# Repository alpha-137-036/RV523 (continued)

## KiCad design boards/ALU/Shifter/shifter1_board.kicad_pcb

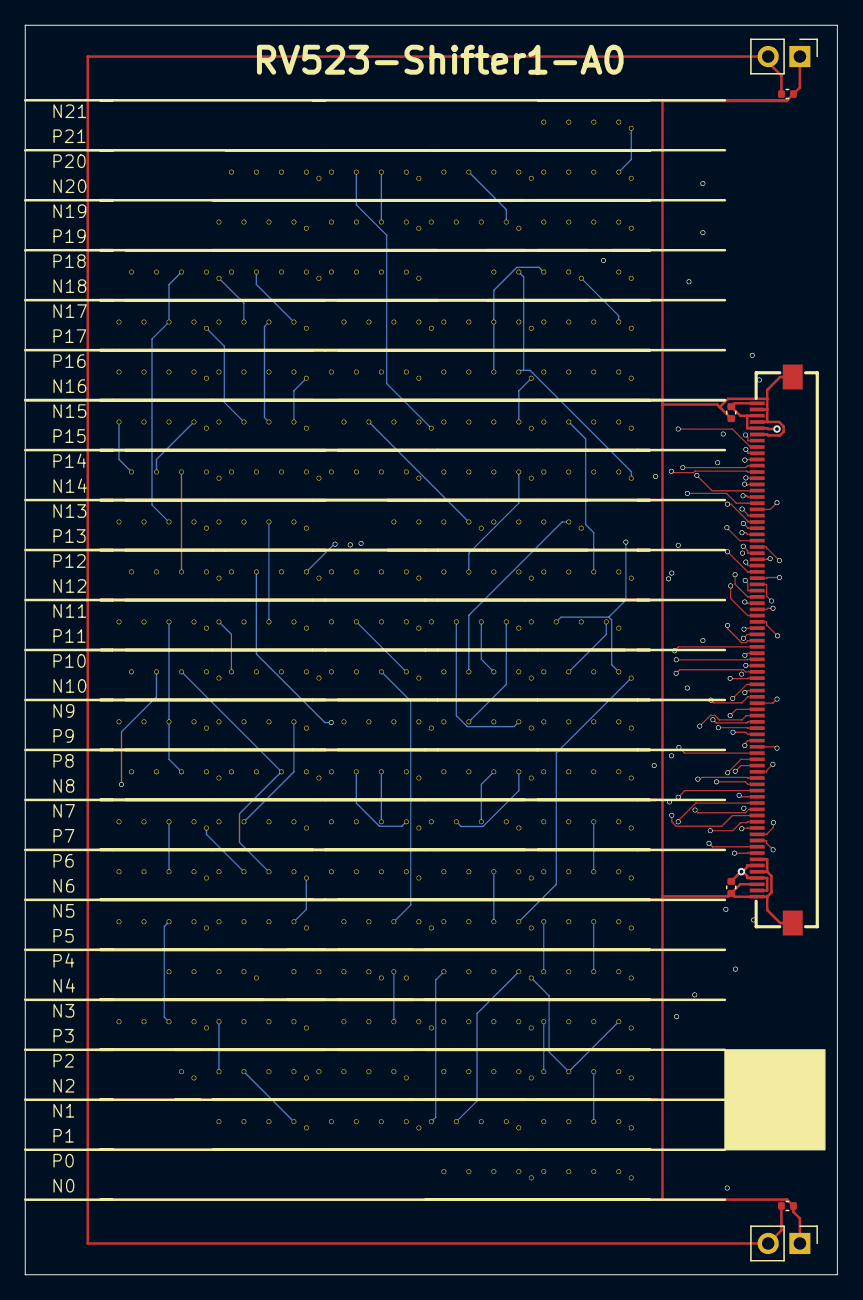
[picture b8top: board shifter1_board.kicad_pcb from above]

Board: 4 copper layers, 65.0 x 100.0 mm, 172 parts (0 on the bottom side), 138 nets.

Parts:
C1, C2, C3, C4: C_0402_1005Metric
j1: FPC-SMD_THD0518-80CL-GF
j2, j3: PinHeader_1x02_P2.54mm_Vertical
sh1._185_, sh1._186_, sh1._187_, sh1._188_, sh1._189_, sh1._190_, sh1._191_, sh1._192_, sh1._193_, sh1._194_, sh1._195_, sh1._196_, sh1._197_, sh1._198_, sh1._199_, sh1._200_, sh1._201_, sh1._202_, sh1._203_, sh1._204_, sh1._205_, sh1._206_, sh1._207_, sh1._208_, sh1._209_, sh1._210_, sh1._211_, sh1._212_, sh1._213_, sh1._214_, sh1._215_, sh1._216_, sh1._220_, sh1._221_, sh1._222_, sh1._223_, sh1._224_, sh1._225_, sh1._226_, sh1._227_, sh1._228_, sh1._229_, sh1._230_, sh1._231_, sh1._232_, sh1._233_, sh1._234_, sh1._235_, sh1._236_, sh1._237_, sh1._238_, sh1._239_, sh1._240_, sh1._241_, sh1._242_, sh1._243_, sh1._244_, sh1._245_, sh1._246_, sh1._247_, sh1._248_, sh1._249_, sh1._250_, sh1._251_, sh1._252_, sh1._253_, sh1._254_, sh1._255_, sh1._256_, sh1._257_, sh1._258_, sh1._259_, sh1._260_, sh1._261_, sh1._262_, sh1._263_, sh1._264_, sh1._265_, sh1._266_, sh1._267_, sh1._268_, sh1._269_, sh1._270_, sh1._271_, sh1._272_, sh1._273_, sh1._274_, sh1._275_, sh1._276_, sh1._277_, sh1._278_, sh1._279_, sh1._280_, sh1._281_, sh1._282_, sh1._283_: AOI22
sh1._217_, sh1._218_, sh1._219_: NOT
sh1.decap0_L, sh1.decap0_M, sh1.decap0_R, sh1.decap1_L, sh1.decap1_M, sh1.decap1_R, sh1.decap2_L, sh1.decap2_M, sh1.decap2_R, sh1.decap3_L, sh1.decap3_M, sh1.decap3_R, sh1.decap4_L, sh1.decap4_M, sh1.decap4_R, sh1.decap5_L, sh1.decap5_M, sh1.decap5_R, sh1.decap6_L, sh1.decap6_M, sh1.decap6_R, sh1.decap7_L, sh1.decap7_M, sh1.decap7_R, sh1.decap8_L, sh1.decap8_M, sh1.decap8_R, sh1.decap9_L, sh1.decap9_M, sh1.decap9_R, sh1.decap10_L, sh1.decap10_M, sh1.decap10_R, sh1.decap11_L, sh1.decap11_M, sh1.decap11_R, sh1.decap12_L, sh1.decap12_M, sh1.decap12_R, sh1.decap13_L, sh1.decap13_M, sh1.decap13_R, sh1.decap14_L, sh1.decap14_M, sh1.decap14_R, sh1.decap15_L, sh1.decap15_M, sh1.decap15_R, sh1.decap16_L, sh1.decap16_M, sh1.decap16_R, sh1.decap17_L, sh1.decap17_M, sh1.decap17_R, sh1.decap18_L, sh1.decap18_M, sh1.decap18_R, sh1.decap19_L, sh1.decap19_M, sh1.decap19_R, sh1.decap20_L, sh1.decap20_M, sh1.decap20_R, sh1.decap21_L, sh1.decap21_M, sh1.decap21_R: DECAP

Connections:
A0: j1.74 (pins.74), sh1._219_.A, sh1._252_.B2, sh1._263_.B2
A.0: j1.71 (pins.71), sh1._193_.B1, sh1._200_.A2
A.1: j1.69 (pins.69), sh1._192_.B2, sh1._211_.A2
A.2: j1.67 (pins.67), sh1._190_.A2, sh1._191_.B2
A.3: j1.65 (pins.65), sh1._189_.B2, sh1._194_.A2
A.4: j1.63 (pins.63), sh1._188_.B2, sh1._195_.A2
A.5: j1.61 (pins.61), sh1._187_.B2, sh1._196_.A2
A.6: j1.59 (pins.59), sh1._186_.B2, sh1._197_.A2
A.7: j1.57 (pins.57), sh1._185_.B2, sh1._198_.A2
A.8: j1.55 (pins.55), sh1._199_.A2, sh1._216_.B2
A.9: j1.53 (pins.53), sh1._201_.A2, sh1._215_.B2
A.10: j1.51 (pins.51), sh1._202_.A2, sh1._214_.B2
A.11: j1.49 (pins.49), sh1._203_.A2, sh1._213_.B2
A.12: j1.47 (pins.47), sh1._204_.A2, sh1._212_.B2
A.13: j1.45 (pins.45), sh1._205_.A2, sh1._210_.B2
A.14: j1.43 (pins.43), sh1._206_.A2, sh1._209_.B2
A.15: j1.41 (pins.41), sh1._207_.A2, sh1._208_.B2
A.16: j1.39 (pins.39), sh1._207_.B2, sh1._208_.A2
A.17: j1.37 (pins.37), sh1._206_.B2, sh1._209_.A2
A.18: j1.35 (pins.35), sh1._205_.B2, sh1._210_.A2
A.19: j1.33 (pins.33), sh1._204_.B2, sh1._212_.A2
A.20: j1.31 (pins.31), sh1._203_.B2, sh1._213_.A2
A.21: j1.29 (pins.29), sh1._202_.B2, sh1._214_.A2
A.22: j1.27 (pins.27), sh1._201_.B2, sh1._215_.A2
A.23: j1.25 (pins.25), sh1._199_.B2, sh1._216_.A2
A.24: j1.23 (pins.23), sh1._185_.A2, sh1._198_.B2
A.25: j1.21 (pins.21), sh1._186_.A2, sh1._197_.B2
A.26: j1.19 (pins.19), sh1._187_.A2, sh1._196_.B2
A.27: j1.17 (pins.17), sh1._188_.A2, sh1._195_.B2
A.28: j1.15 (pins.15), sh1._189_.A2, sh1._194_.B2
A.29: j1.13 (pins.13), sh1._190_.B2, sh1._191_.A2
A.30: j1.11 (pins.11), sh1._192_.A2, sh1._211_.B2
A.31: j1.9 (pins.9), sh1._193_.A2, sh1._200_.B2
B.0: sh1._217_.A, sh1._220_.B1, sh1._221_.B1, sh1._222_.B1, sh1._223_.B1, sh1._224_.B1, sh1._225_.B1, sh1._226_.B1, sh1._227_.B1, sh1._228_.B1, sh1._229_.B1, sh1._230_.B1, sh1._231_.B1, sh1._232_.B1, sh1._233_.B1, sh1._234_.B1, sh1._235_.B1, sh1._236_.B1, sh1._237_.B1, sh1._238_.B1, sh1._239_.B1, sh1._240_.B1, sh1._241_.B1, sh1._242_.B1, sh1._243_.B1, sh1._244_.B1, sh1._245_.B1, sh1._246_.B1, sh1._247_.B1, sh1._248_.B1, sh1._249_.B1, sh1._250_.B1, sh1._251_.B1
B.1: sh1._218_.A, sh1._252_.B1, sh1._253_.B1, sh1._254_.B1, sh1._255_.B1, sh1._256_.B1, sh1._257_.B1, sh1._258_.B1, sh1._259_.B1, sh1._260_.B1, sh1._261_.B1, sh1._262_.B1, sh1._263_.B1, sh1._264_.B1, sh1._265_.B1, sh1._266_.B1, sh1._267_.B1, sh1._268_.B1, sh1._269_.B1, sh1._270_.B1, sh1._271_.B1, sh1._272_.B1, sh1._273_.B1, sh1._274_.B1, sh1._275_.B1, sh1._276_.B1, sh1._277_.B1, sh1._278_.B1, sh1._279_.B1, sh1._280_.B1, sh1._281_.B1, sh1._282_.B1, sh1._283_.B1
F.0: j1.70 (pins.70), sh1._252_.Y
F.1: j1.68 (pins.68), sh1._263_.Y
F.2: j1.66 (pins.66), sh1._274_.Y
F.3: j1.64 (pins.64), sh1._277_.Y
F.4: j1.62 (pins.62), sh1._278_.Y
F.5: j1.60 (pins.60), sh1._279_.Y
F.6: j1.58 (pins.58), sh1._280_.Y
F.7: j1.56 (pins.56), sh1._281_.Y
F.8: j1.54 (pins.54), sh1._282_.Y
F.9: j1.52 (pins.52), sh1._283_.Y
F.10: j1.50 (pins.50), sh1._253_.Y
F.11: j1.48 (pins.48), sh1._254_.Y
F.12: j1.46 (pins.46), sh1._255_.Y
F.13: j1.44 (pins.44), sh1._256_.Y
F.14: j1.42 (pins.42), sh1._257_.Y
F.15: j1.40 (pins.40), sh1._258_.Y
F.16: j1.38 (pins.38), sh1._259_.Y
F.17: j1.36 (pins.36), sh1._260_.Y
F.18: j1.34 (pins.34), sh1._261_.Y
F.19: j1.32 (pins.32), sh1._262_.Y
F.20: j1.30 (pins.30), sh1._264_.Y
F.21: j1.28 (pins.28), sh1._265_.Y
F.22: j1.26 (pins.26), sh1._266_.Y
F.23: j1.24 (pins.24), sh1._267_.Y
F.24: j1.22 (pins.22), sh1._268_.Y
F.25: j1.20 (pins.20), sh1._269_.Y
F.26: j1.18 (pins.18), sh1._270_.Y
F.27: j1.16 (pins.16), sh1._271_.Y
F.28: j1.14 (pins.14), sh1._272_.Y
F.29: j1.12 (pins.12), sh1._273_.Y
F.30: j1.10 (pins.10), sh1._275_.Y
F.31: j1.8 (pins.8), sh1._276_.Y
GND: C1.1, C2.1, C3.1, C4.1, j1.1 (pins.1), j1.3 (pins.3), j1.5 (pins.5), j1.7 (pins.7), j1.75 (pins.75), j1.77 (pins.77), j1.79 (pins.79), j1.81 (pins.81), j1.82 (pins.82), j2.1 (pins.1), j3.1 (pins.1)
VDD: C1.2, C2.2, C3.2, C4.2, j1.2 (pins.2), j1.4 (pins.4), j1.6 (pins.6), j1.76 (pins.76), j1.78 (pins.78), j1.80 (pins.80), j2.2 (pins.2), j3.2 (pins.2)
pins.71: j1.72 (pins.72), sh1._185_.A1, sh1._186_.A1, sh1._187_.A1, sh1._188_.A1, sh1._189_.A1, sh1._190_.A1, sh1._191_.A1, sh1._192_.A1, sh1._193_.A1, sh1._194_.A1, sh1._195_.A1, sh1._196_.A1, sh1._197_.A1, sh1._198_.A1, sh1._199_.A1, sh1._200_.A1, sh1._201_.A1, sh1._202_.A1, sh1._203_.A1, sh1._204_.A1, sh1._205_.A1, sh1._206_.A1, sh1._207_.A1, sh1._208_.A1, sh1._209_.A1, sh1._210_.A1, sh1._211_.A1, sh1._212_.A1, sh1._213_.A1, sh1._214_.A1, sh1._215_.A1, sh1._216_.A1
pins.72: j1.73 (pins.73), sh1._185_.B1, sh1._186_.B1, sh1._187_.B1, sh1._188_.B1, sh1._189_.B1, sh1._190_.B1, sh1._191_.B1, sh1._192_.B1, sh1._193_.B2, sh1._194_.B1, sh1._195_.B1, sh1._196_.B1, sh1._197_.B1, sh1._198_.B1, sh1._199_.B1, sh1._200_.B1, sh1._201_.B1, sh1._202_.B1, sh1._203_.B1, sh1._204_.B1, sh1._205_.B1, sh1._206_.B1, sh1._207_.B1, sh1._208_.B1, sh1._209_.B1, sh1._210_.B1, sh1._211_.B1, sh1._212_.B1, sh1._213_.B1, sh1._214_.B1, sh1._215_.B1, sh1._216_.B1
sh1._035_: sh1._200_.Y, sh1._220_.A2, sh1._231_.B2
sh1._036_: sh1._202_.Y, sh1._221_.A2, sh1._222_.B2
sh1._037_: sh1._203_.Y, sh1._222_.A2, sh1._223_.B2
sh1._038_: sh1._204_.Y, sh1._223_.A2, sh1._224_.B2
sh1._039_: sh1._205_.Y, sh1._224_.A2, sh1._225_.B2
sh1._040_: sh1._206_.Y, sh1._225_.A2, sh1._226_.B2
sh1._041_: sh1._207_.Y, sh1._226_.A2, sh1._227_.B2
sh1._042_: sh1._208_.Y, sh1._227_.A2, sh1._228_.B2
sh1._043_: sh1._209_.Y, sh1._228_.A2, sh1._229_.B2
sh1._044_: sh1._210_.Y, sh1._229_.A2, sh1._230_.B2
sh1._045_: sh1._212_.Y, sh1._230_.A2, sh1._232_.B2
sh1._046_: sh1._211_.Y, sh1._231_.A2, sh1._242_.B2
sh1._047_: sh1._213_.Y, sh1._232_.A2, sh1._233_.B2
sh1._048_: sh1._214_.Y, sh1._233_.A2, sh1._234_.B2
sh1._049_: sh1._215_.Y, sh1._234_.A2, sh1._235_.B2
sh1._050_: sh1._216_.Y, sh1._235_.A2, sh1._236_.B2
sh1._051_: sh1._185_.Y, sh1._236_.A2, sh1._237_.B2
sh1._052_: sh1._186_.Y, sh1._237_.A2, sh1._238_.B2
sh1._053_: sh1._187_.Y, sh1._238_.A2, sh1._239_.B2
sh1._054_: sh1._188_.Y, sh1._239_.A2, sh1._240_.B2
sh1._055_: sh1._189_.Y, sh1._240_.A2, sh1._241_.B2
sh1._056_: sh1._191_.Y, sh1._241_.A2, sh1._243_.B2
sh1._057_: sh1._190_.Y, sh1._242_.A2, sh1._245_.B2
sh1._058_: sh1._192_.Y, sh1._243_.A2, sh1._244_.B2
sh1._059_: sh1._193_.Y, sh1._244_.A2
sh1._060_: sh1._194_.Y, sh1._245_.A2, sh1._246_.B2
sh1._061_: sh1._195_.Y, sh1._246_.A2, sh1._247_.B2
sh1._062_: sh1._196_.Y, sh1._247_.A2, sh1._248_.B2
sh1._063_: sh1._197_.Y, sh1._248_.A2, sh1._249_.B2
sh1._064_: sh1._198_.Y, sh1._249_.A2, sh1._250_.B2
sh1._065_: sh1._199_.Y, sh1._250_.A2, sh1._251_.B2
sh1._066_: sh1._201_.Y, sh1._221_.B2, sh1._251_.A2
sh1._067_: sh1._219_.Y, sh1._220_.B2
sh1._068_: sh1._217_.Y, sh1._220_.A1, sh1._221_.A1, sh1._222_.A1, sh1._223_.A1, sh1._224_.A1, sh1._225_.A1, sh1._226_.A1, sh1._227_.A1, sh1._228_.A1, sh1._229_.A1, sh1._230_.A1, sh1._231_.A1, sh1._232_.A1, sh1._233_.A1, sh1._234_.A1, sh1._235_.A1, sh1._236_.A1, sh1._237_.A1, sh1._238_.A1, sh1._239_.A1, sh1._240_.A1, sh1._241_.A1, sh1._242_.A1, sh1._243_.A1, sh1._244_.A1, sh1._245_.A1, sh1._246_.A1, sh1._247_.A1, sh1._248_.A1, sh1._249_.A1, sh1._250_.A1, sh1._251_.A1
sh1._069_: sh1._218_.Y, sh1._252_.A1, sh1._253_.A1, sh1._254_.A1, sh1._255_.A1, sh1._256_.A1, sh1._257_.A1, sh1._258_.A1, sh1._259_.A1, sh1._260_.A1, sh1._261_.A1, sh1._262_.A1, sh1._263_.A1, sh1._264_.A1, sh1._265_.A1, sh1._266_.A1, sh1._267_.A1, sh1._268_.A1, sh1._269_.A1, sh1._270_.A1, sh1._271_.A1, sh1._272_.A1, sh1._273_.A1, sh1._274_.A1, sh1._275_.A1, sh1._276_.A1, sh1._277_.A1, sh1._278_.A1, sh1._279_.A1, sh1._280_.A1, sh1._281_.A1, sh1._282_.A1, sh1._283_.A1
sh1._073_.0: sh1._220_.Y, sh1._252_.A2, sh1._274_.B2
sh1._073_.1: sh1._231_.Y, sh1._263_.A2, sh1._277_.B2
sh1._073_.2: sh1._242_.Y, sh1._274_.A2, sh1._278_.B2
sh1._073_.3: sh1._245_.Y, sh1._277_.A2, sh1._279_.B2
sh1._073_.4: sh1._246_.Y, sh1._278_.A2, sh1._280_.B2
sh1._073_.5: sh1._247_.Y, sh1._279_.A2, sh1._281_.B2
sh1._073_.6: sh1._248_.Y, sh1._280_.A2, sh1._282_.B2
sh1._073_.7: sh1._249_.Y, sh1._281_.A2, sh1._283_.B2
sh1._073_.8: sh1._250_.Y, sh1._253_.B2, sh1._282_.A2
sh1._073_.9: sh1._251_.Y, sh1._254_.B2, sh1._283_.A2
sh1._073_.10: sh1._221_.Y, sh1._253_.A2, sh1._255_.B2
sh1._073_.11: sh1._222_.Y, sh1._254_.A2, sh1._256_.B2
sh1._073_.12: sh1._223_.Y, sh1._255_.A2, sh1._257_.B2
sh1._073_.13: sh1._224_.Y, sh1._256_.A2, sh1._258_.B2
sh1._073_.14: sh1._225_.Y, sh1._257_.A2, sh1._259_.B2
sh1._073_.15: sh1._226_.Y, sh1._258_.A2, sh1._260_.B2
sh1._073_.16: sh1._227_.Y, sh1._259_.A2, sh1._261_.B2
sh1._073_.17: sh1._228_.Y, sh1._260_.A2, sh1._262_.B2
sh1._073_.18: sh1._229_.Y, sh1._261_.A2, sh1._264_.B2
sh1._073_.19: sh1._230_.Y, sh1._262_.A2, sh1._265_.B2
sh1._073_.20: sh1._232_.Y, sh1._264_.A2, sh1._266_.B2
sh1._073_.21: sh1._233_.Y, sh1._265_.A2, sh1._267_.B2
sh1._073_.22: sh1._234_.Y, sh1._266_.A2, sh1._268_.B2
sh1._073_.23: sh1._235_.Y, sh1._267_.A2, sh1._269_.B2
sh1._073_.24: sh1._236_.Y, sh1._268_.A2, sh1._270_.B2
sh1._073_.25: sh1._237_.Y, sh1._269_.A2, sh1._271_.B2
sh1._073_.26: sh1._238_.Y, sh1._270_.A2, sh1._272_.B2
sh1._073_.27: sh1._239_.Y, sh1._271_.A2, sh1._273_.B2
sh1._073_.28: sh1._240_.Y, sh1._272_.A2, sh1._275_.B2
sh1._073_.29: sh1._241_.Y, sh1._273_.A2, sh1._276_.B2
sh1._073_.30: sh1._243_.Y, sh1._275_.A2
sh1._073_.31: sh1._244_.Y, sh1._276_.A2

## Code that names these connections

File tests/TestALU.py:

from ALU import ALU
from testboard import TestBoard
from time import sleep

alu = ALU()
testboard = TestBoard()

alu.connectTestBoard(testboard, 8)

alu.enableLEDs(True)


alu.A = 0xA5
alu.B = 0x5A
alu.Cin = 0

# while True:
#     alu.ADD = 0
#     sleep(0.20)
#     alu.ADD = 1
#     sleep(0.20)

doSweep = True

alu.ADD = 1
alu.XOR = 1
alu.AND = 0
alu.SUB = 0
alu.nSET0 = 0

if doSweep:
    for A in range(1 << alu.N):
        for B in range(1 << alu.N):
            alu.A = A
            alu.B = B
            print(f"A = {A}, B={B} ==> S={alu.S}")
else:
    alu.A = 0x5A
    alu.B = 0x33

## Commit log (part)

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2025-05-17 First version
2025-05-17 pin headers (2*17 and 2*8)
2025-05-18 Routing complete. Corrected some errors
2025-05-18 ^Move origin. Lines between all slices
2025-05-18 Schematic for 8-bit ALU
2025-05-18 schematic with solder jumpers for S31/C31
2025-05-18 Attempt to design the 8-bit ALU PCB
2025-05-19 Routed PCB. BUT SetBit0 is missing !
2025-05-19 Mounting holes. PCB title.
2025-06-09 Improve look of the bus pin numbers
2025-06-09 Cosmetic improvement of the silkscreen (position of annotations for the 2x1 pin headers)
2025-06-09 Re-route with wider tracks and vias, to avoid "Danger" notifications from JLCPCB.
2025-06-09 Pass-through connectors. Partial manual routing.
2025-06-09 Final version. Stopped trying to correct the thermal relief error. This is apparently not needed with solder reflow
2025-06-09 Remove some loose tracks
2025-06-09 Oups, orientation of the MCP23017 chips was somehow wrong by 180 degrees ! Thanks JLCPCB for their component viewer !!
2025-06-09 Manual routing the main bus
2025-06-09 Use larger vias. Auto-routing is still working !! That's good placement :)
2025-06-09 Yes: complete auto-routing; "stick" form factor. Silk screen complete.
2025-06-09 First version of TestBoard. Lacking the 2.54mm pin headers
2025-06-09 Production files
2025-06-09 Complete routing. BEAUTIFUL !!!
2025-06-09 Manual routing and SSOP. Only routed the signal lines. Beautiful, isn't it ?
2025-06-09 Fine tuning the PCB
2025-06-09 Attempt to resolve one more solder mask / pad violation
2025-06-09 Don't make silk screen overlap with pads. Horror: I realized the auo-router has NOT completed its job.... many connections are not done !
2025-06-09 Bus pin silkscreen labels
2025-06-14 Variant of test board with 4 20P connectors rather than 1 80P
2025-06-14 Silkscreen cleanup. Production files.
2025-06-14 Use M2 mounting holes rather than 2.5mm holes
2025-06-28 New idea: implementation using only MOSFET transistors ! Spice simulation of ALU...
2025-07-01 First steps to design a "standard cell library" of cells using only discrete transistors.
    Project trajectory is changing !
2025-07-01 Experiments with a Verilog->Kicad workshop
2025-07-02 NOT layout
2025-07-02 All gates layout on a strict 2.5mm grid. Flipped versions of all three layouts
2025-07-02 Update footprint to better match the layout. Use silkscreen to describe the power rails
2025-07-02 First prototype for the generator of the final board
2025-07-03 flip the cells to share power lines
2025-07-13 Move standard cell library to lib/ NOR Refined yosys to kicad netlist converter
2025-07-13 Analog simulation of NAND3 cell
2025-07-13 NOR3 cell with spice simulation and PCB design
2025-07-13 NOT cell: spice simulation, netlist generation
2025-07-13 Generate spice circuit using python script
2025-07-13 same for NAND3
2025-07-13 same for NAND
2025-07-13 Automate better the generation of test vectors
2025-07-13 Move pin definition to gate's physical .v
2025-07-13 OAI22 cell
2025-07-14 Update pin names in behavioral verilog
2025-07-14 OAI21 cell
2025-07-14 AOI211 cell
2025-07-14 OAI211 cell
2025-07-14 Footprints for all implemented cells
2025-07-14 Somehow NAND PCB was botched. Changed pin position of B, too
2025-07-14 The layout of the NOT gate was also botched (PMOS pinout wrong)
2025-07-14 First tries toward flip-flop and latches: SR_LATCH cell
2025-07-14 D_LATCH, with tests
2025-07-14 High-density layout with pitch of 1.1mm, which gains 23% !!
2025-07-15 Update AOI22 footprint
2025-07-15 Update OAI22 footprint
2025-07-15 Update OAI21 footprint
2025-07-15 Update NAND3 footprint
2025-07-15 Update NAND footprint
2025-07-15 Update NOR footprint
2025-07-15 Update NOT footprint
2025-07-15 Experiments on ALU
2025-07-15 DECAP pseudo-cell
2025-07-15 Continue refactoring
2025-07-15 TINV Tristate Inverter (no test yet)
2025-07-16 D_LATCH now uses TINV
2025-07-16 Rename EN/nEN into CLK/nCLK for D_LATCH
2025-07-20 Rename NAND into NAND2 and its inputs A and B into A1 and A2 (general convention when the pins can be swapped)
2025-07-20 Same for NOR->NOR2
2025-07-20 Same for NOR3
2025-07-20 Conversion tool had a bug
2025-07-20 Add thresholds to RV523.lib, this seems to be necessary for the placer
2025-07-20 Version script to autoplace using OpenROAD
2025-07-23 Y pad was misplaced
2025-07-23 NAND4 gate
2025-07-23 NAND4 and NOR4 footprints
2025-07-23 Unlock tracks in OAI211
2025-07-25 Footprint of all cells now use 1mm*4mm grid rather than 1.1mm*4.4mm
2025-07-25 New grid pitch
2025-07-25 Experiment with pads at Y=1.8/2.2 rather than 1.7/2.3 and not moving the transistors up and down, otherwise, Y-clearance of 0.4mm cannot be ensured
2025-07-25 Make the pads of my SOT523 footprint very slightly smaller, which is enough to route all the cells and leave the mosfets exactly on the grid
2025-07-26 Add the value "NMOS" and "PMOS" to the transistor modules
2025-07-26 Propagate MOSFET values to the cells' PCBs
2025-07-26 One updated netlist missing
2025-07-26 git-ignore kicad_prl files and fp-info-cache and *-backups
2025-07-26 DECAP_LED cell, combining a DECAP and a LED
2025-07-26 Set value of decap
2025-07-26 Footprint of TINV
2025-07-26 Behavioral model of TINV
2025-07-27 RV523_MOSFETS.v uses our own footprint
2025-07-27 Cell test board: all components placed and routed, except supply rails.
2025-07-27 Slightly move the CAP in de DECAP cell to avoid DRC violation when put next to a NOT cell
2025-07-27 Pad Y of OAI21 flipped was not properly connected
2025-07-27 process_board.py: all references to footprints within cells are made unique
2025-07-27 Add placeholder for the board barcode and add board title
2025-07-27 Manual add LCSC references. Remove connectors from the BOM and positions file
2025-07-27 The files finally sent to production !
2025-08-06 Don't include the transistor models from the cell spice circuits. Explicit power pins in the spice circuits
2025-08-06 Don't hardcode 3.3V as VDD; but use the {vdd} parameter
2025-08-06 Regenerate AOI21 circuit and test circuit
2025-08-06 Regenerate AOI211 netlist and test circuit
2025-08-06 Regenerate NAND3 netlist and test circuit
2025-08-06 Regenerate NAND4 netlist and test circuit
2025-08-06 Regenerate NOR3 netlist and test circuit
2025-08-06 Regenerate NOT netlist and test circuit
2025-08-06 Regenerate OAI21 netlist and test circuit
2025-08-06 Regenerate OAI211 netlist and test circuit
2025-08-06 Regenerate SR_LATCH netlist
2025-08-06 Regenerate D_LATCH netlist and test circuit
2025-08-06 Regenerate SRAM_CELL netlist
2025-08-07 Set nominal voltage to 5V, remove VPW and VNW pins. Eventually, this will be modifications of CharLib.
2025-08-07 Add a BUF cell to RV523.lib file.
2025-08-07 AND2 cell
2025-08-07 Python script generates yosys script itself, as it's always the same
2025-08-07 generate_all_netlists.py script now colelcts behavioral verilog files from each cell and generates RV523_behavioral.v
2025-08-08 Add AND2 to the cell list
2025-08-08 D_LATCH_DUAL_READ_PORT.kicad_pcb: some missing tracks
2025-08-10 Rename cellList.json5 into RV523_cells.json5
2025-08-10 XOR2 cell
2025-08-10 XNOR2 cell
2025-08-10 Script to characterize all cells with CharLib
2025-08-10 Fail on first yosys error
2025-08-10 AND4 cell
2025-08-10 MUX2 cell
2025-08-10 AOI221 and AOI222 cells
2025-08-10 OAI31 and OAI32 cells
2025-08-11 10T XNOR2 gate
2025-08-11 10T XOR2 gate
2025-08-12 Rename and reorder AOI21 pins to align with sky130 cell. PCB layout and footprint not yet adjusted.
2025-08-12 Update AOI21 test circuit
2025-08-12 Script to generate Kicad footprints
2025-08-12 XOR2 layout. That one was tricky !!
2025-08-12 AOI2111 cell
2025-08-12 NAND2B cell
2025-08-12 AND4B cell
2025-08-12 MAJ3 and OA21 cells
2025-09-23 First attempt to modelize the real SOT-523 transistors
2025-09-23 re-characterize all the cells
2025-09-27 Add some more loads and more realistic slew rates
2025-09-27 AOI311 and OA21 Kicad footprints
2025-09-27 32-bit adder in 763ns (Sklansky)
2025-09-29 Configure the ADD vs XOR operation (carry_propagate or not). 396T - 777.01ns propagation delay.
2025-09-29 Improved ALU8: select XOR/AND/OR in last stage. 444T - 699.43ns
2025-10-03 Use 2SK3019 for N-channel transistors
2025-10-03 Fix pin names of OAI221
2025-10-03 Re-characterize the whole library, at 3.3V.
2025-10-05 Superfluous comma (causes a iverilog warning)
2025-10-05 Generate waveforms for comparator_tb
2025-10-06 comparator_board is routed
2025-10-06 OA21 PCB
2025-10-06 AND3 PCB
2025-10-06 OAI32 PCB
2025-10-07 Comparator board. First version submitted to JLCPCB.
2025-10-19 XNOR2 PCB: useless small track
2025-11-02 First version of full ALU, made of four different boards
2025-11-03 Test all ALU. Fix a few bugs
2025-11-03 Fix cla.constraints.sdc
2025-11-03 More tweaking. Let the synthesizer select the gates for swapper and cla, but NOT for shift_stage !!
2025-11-03 alu_final generates A0 for shifting
2025-11-08 Define manufacturing grid (otherwise DRT crashes). Define via layers and shapes.
2025-11-08 Synthesize with a different version of yosys/abc
2025-11-08 First attempt to place and route shifter1
2025-11-09 Renaming
2025-11-09 Shifter1 placement as CSV file with Kicad coordinates
2025-11-09 Start shifter1 board
2025-11-10 Placement, performed by freerouting
2025-11-10 Add DECAP manually to RV523.lib and RV523.lef file
2025-11-10 Fixed position of pin Y of XNOR2 gate in RV523.lef
2025-11-12 Fully routed board, including final board. GND and VDD fill zones
2025-11-16 Cell netlists can now include resistors and capacitors, with the value as a parameter.
2025-11-16 New cell: DELAY80: a buffer with a large delay (around 80ns), based on a RC circuit.
2025-11-20 Start RTL of the full CPU
2025-11-20 Decoding immediate operands
2025-11-21 Decoding of register indexes in ID stage. Disassembly of the instruction in the ID stage.
2025-11-21 Decode and implement all ALU operations
2025-11-22 Inject NOP in the pipeline when reset line is low
2025-11-22 Don't pass reg_write signal in the pipeline. Just use rd_idx=0. Write-back stage is functional !
2025-11-22 Improve tracing of forwards
2025-11-22 Branch logic
2025-11-23 Register file must be "write-before-read"!
2025-11-23 Proper bubble insertion from IF stage on reset and branch
2025-11-23 Properly connect the D-bus
2025-11-23 Load-Use hazard handling by stalling the pipeline at the ID stage. Sanitize rd_idx for bubbles
2025-11-23 Bug fix in pipeline stalling in IF stage
2025-11-23 Bug fix in decoding rs2_idx
2025-11-24 Refactoring of trace signals towards <stage>_trc_<name>. These signals are only for the simulation
2025-11-24 Improved a lot the traces: disassembly at all stages.
2025-11-24 Improve trace at ID stage
2025-11-24 Much larger timeout
2025-11-24 Better trace when EBREAK is reached
2025-11-24 Simple test in C
2025-11-26 Bug fix in the memory tracking ! backtrace now works much better...
2025-11-27 Implementation of Byte and Half-word load/stores, including sign vs zero extension on load
2025-11-29 Test of byte/half-word signed/unsigned loads and stores
2025-11-29 Simple "output" peripheral and simple interconnect on the data bus
2025-11-29 RODATA ROM memory at address 0x10000000
2025-11-30 Bug fix ! Do not stall the pipeline when we're handling a branch hazard at the same time. Otherwise, the instruction following the branch gets incorrectly executed !
2025-11-30 Count and report cycles and instructions
2025-11-30 Write output to a file
2025-11-30 Resolve branch in EX stage instead of MEM stage. This makes the EX stage a bit longer, but gains one cycle for each branch. On the printf test, it gains 12% cycles :)
2025-11-30 No need for mem_bxx
2025-11-30 Move some muxes to the EX stage, where normally their timing is for free, once the branch resolution is in EX anyway. This reduces the number of ports to the MEM stage and the corresponding number of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
2025-12-01 Fix name of signals and missing declaration. Somehow iverilog accepts this..... (but complains about trailing commas, go figure...)
2025-12-01 Add a default to a case. Otherwise, the synthesizer will believe it's a latch
2025-12-04 Top-level id_bubble signal, instead of using illegal opcode
2025-12-10 Synthesis of IF_transitions module
2025-12-25 Add a RV delay to every D_LATCH. This helps alleviate any hold time violations.
2025-12-25 Manually-written PULSED_DFF circuit
2025-12-26 Circuits to measure input capacitances
2025-12-26 Output tables ready to paste in liberty file
2025-12-26 Manually paste PULSED_DFF data in liberty file and associated files
